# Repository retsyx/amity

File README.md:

# Amity
HDMI-CEC that works!

Control your home theater with a familiar remote, and integrate it with HomeKit or Home Assistant home automation systems.

Read the [rationale](doc/rationale.md), to know why Amity uses HDMI-CEC, and how it works.

## Prerequisites

* A Raspberry Pi 3 Model B+, or Pi Zero 2 W, or newer, that can run 64-bit Linux; with an appropriate power supply. Network connectivity is required for initial setup but not when controlling your home theater.
* A MicroSD card (4GB or larger).
* A remote control. See the [list of supported remotes](doc/supported-remotes.md).
* An [Amity Fin](hw/README.md) and an extra HDMI cable.

## Caveats

### Use Amity at Your Own Risk

!!! Using Amity may destroy your expensive HDMI equipment. Proceed at your own risk !!!

While Amity has been tested and has worked reliably with some HDMI equipment, there may still be a risk from unknown bugs. Also, when putting together Amity, you may make a mistake - this may destroy your HDMI equipment and/or your Raspberry Pi.

!!! Using Amity may destroy your expensive HDMI equipment. Proceed at your own risk !!!

### Amity is an HDMI-CEC Controller (Not a Universal Remote)

Amity is designed for a traditional setup centered around an audio/video receiver (AVR). For example, a TV connected to a receiver output, and various playback devices (i.e. media streamers, blu-ray players, and game consoles, etc.) connected to the receiver's inputs. When changing the source, the input is changed on the receiver. The HDMI-CEC protocol only allows the designated TV to select sources or devices to declare themselves as active sources. TVs do not heed arbitrary source selection commands from other devices. As a result, Amity cannot select inputs on a TV, and cannot control sources connected directly to a TV, including built-in smart TV apps. Similarly, Amity does not support HDMI ARC/eARC. If you use smart TV apps or connect devices, other than a receiver, directly to the TV inputs, Amity is not for your system.

Amity can only control devices that support HDMI-CEC! However, devices that don't support HDMI-CEC (old game consoles, for example) can still be facilitated.

### Amity is a Proof of Concept

HDMI-CEC is unevenly implemented by different manufacturers, so it doesn't always work as expected. At present, Amity can be considered a proof of concept because of the limited set of equipment it has been tested with. It works for me. It may work flawlessly with your equipment, or it may very well not. There may be ways to fix issues you encounter, and there may not. As more equipment is tested with Amity, its utility will become clearer.

Equipment that is known to be compatible with Amity:

- LG OLED TV
- Denon AVR-X3400H, AVR-X3900H
- Apple TV 4K
- Sony Playstation 4/5
- Amazon Fire TV (media player)
- Nintendo Switch (see [Strange Devices](#strange-devices))
- Wii (see [Non-HDMI Sources](#non-hdmi-sources))

## Setup

### HDMI Hardware

Amity inserts itself into the HDMI-CEC bus between the TV, and the receiver. The preferred method is to use Amity Fin.

[Acquire Amity Fin before proceeding](hw/README.md).

### Initial Installation

It is assumed that the Raspberry Pi will be a dedicated device for home theater control. It may be possible to run other services on the same Raspberry Pi but it is not supported, and is strongly discouraged.

Installation is performed with [Raspberry Pi Imager 2.0](https://www.raspberrypi.com/software/) or later (earlier versions will not work).

1. In Raspberry Pi Imager, press `App Options` (bottom left of the app).
2. In the App Options popup, press `Edit` to edit the Content Repository.
3. In the Content Repository popup, select `Use custom URL` and paste this URL into the text field: `https://github.com/retsyx/amity/releases/latest/download/amity-os.json`
4. Press `Apply & Restart`.
5. Run through the configuration wizard:
    1. Select the Raspberry Pi device you are going to use.
    2. Select the OS - `Amity`.
    3. Select the MicroSD.
    4. Set the hostname to something memorable, for example `amity`.
    5. Optionally, set localisation or leave as is.
    6. Set the username and password. The username **must** be `pi`.
    7. If using WiFi, set WiFi network information.
    8. Optionally, enable SSH, and set credentials. It is recommended to enable SSH.
6. Write the image to the MicroSD card.
7. Insert the imaged MicroSD into the Raspberry Pi, and wait for it to complete its initial boot sequence. This may take a few minutes, and a few reboots.
8. In your web browser open the Amity administration page. For example, if the hostname in Raspberry Pi Imager was configured as `amity`, then browse to `https://amity.local` (on Mac) or `https://amity` (on Windows).
 * The web browser will prompt that the site may be unsafe. This is because Amity creates a self signed security certificate for encryption. It is safe. Click on the details, and accept that the site is safe.
9. Create the Amity administration user by entering a username and password. These can be anything.
10. Login with the newly created user.

### Amity Fin Configuration

If using Amity Fin, select the 'Advanced' tab. In the 'HDMI Splice' section press the 'Use with Amity Board' button. When done, the status line should read 'Configured for Amity Board'.

### HDMI Connections

Amity connects between the TV and the receiver.

1. Disconnect the HDMI cable connecting the TV input to the receiver's output.
2. Use one HDMI cable to connect the TV's input to the Amity Fin HDMI port marked `TV`.
3. Use a second HDMI cable to connect the receiver output to the Amity Fin HDMI port marked `AVR`.

### Pairing a Remote

[Screenshot](doc/ui-images.md#remotes)

The remote **MUST** be unpaired from any other device. If the remote is paired to another device, like a streamer or TV, it will fail to work with Amity in unpredictable ways. Pairing and unpairing steps for supported remotes are listed [here](doc/supported-remotes.md). Ensure the remote is charged.

1. Select the 'Remotes' tab. The 'Remotes' panel shows if a remote or keyboard is paired, and allows pairing. Press the 'Pair' button. Wait for the initial prompt to start the pairing process on the remote.

2. Hold the remote near the Raspberry Pi.

3. Start the pairing process on the remote (see pairing steps for supported remotes [here](doc/supported-remotes.md)).

4. Follow the prompts.

If successful, the remote has been paired, and is ready for use.

### Activity Configuration

[Screenshot](doc/ui-images.md#hdmi-activities)

Amity uses a concept of activities to organize the different uses of a home theater system, similar to Harmony remotes. Every activity has a source device (i.e. Apple TV, or PlayStation), an audio output device (i.e. a receiver, or TV for volume commands), and a display (typically a TV). The remote's directional buttons are used for activity selection (on remotes that have them, the blue, red, green and yellow color buttons are also used for activity selection). This allows for up to 5 activities - 4 direction buttons and the select button.

Configuring activities is fairly straightforward thanks to HDMI-CEC.

Ensure that all home theater devices have HDMI-CEC enabled, and are discoverable. Select the 'Activities' tab, and press the 'Scan HDMI' button to list all the devices available on HDMI-CEC, and to create a recommended list of activities.

Press 'Save' to save the recommended activities.

The names of the devices are their HDMI On Screen Display (OSD) names, and are used to reference the devices in Amity configuration. Ensure that no two devices share the same name. Duplicate names are not supported, and will lead to confusion, failure, and disappointment.

Devices that don't appear in the list don't have HDMI-CEC enabled or have a very broken HDMI-CEC implementation (i.e. Nintendo Switch) that may only partially work in general.

If no devices are listed, ensure that Amity's HDMI ports are correctly attached.

#### Editing the List of Activities

The order of the activities matters. Each activity is assigned an activation button on the remote based on its position in the list of activities. The assigned activity button (and color button) on the remote is pictured next to the activity name. Read the [usage](#usage) topic to learn more. To re-order activities, press the up or down arrow buttons. To remove an activity, press the 'trash' button for that activity. To add a new activity, press the '+' button at the top of the activity list.

#### Editing an Activity

To edit an activity, press the 'Edit' button of the activity.

The fields of an activity are:

* `Name` - this can be any descriptive name you choose. The activity name is used with [HomeKit](#homekit).
* `Display` - the HDMI OSD name of the display device. Typically a TV.
* `Source` - the HDMI OSD name of the AV source device.
* `Audio` - the HDMI OSD name of the audio output device, typically a receiver.
* `Switch Device` (optional) - See [Strange Devices](#strange-devices)
* `Input` (if `Switch Device` is specified)

Remember to 'Save' the activities when done.

## Usage

Amity has two basic modes, standby, when the home theater is in standby, and active when an activity has been selected.

Note that while Amity supports multi-button and long button presses for additional functionality, the vast majority of users (e.g. family members) can ignore all of it and fully use Amity with simple button presses.

### Standby

In standby, 1 of up to 10 activities can be started. The first 5 activities are assigned to the select, and directional buttons - select, up, right, down, left. Note the order listed here matches the order of activities as specified in the Activities configuration tab. The select button starts the first activity, up the second, right the third, and so on. The next 5 activities are assigned to long presses of the same buttons, in the same order. A long press of the select button starts the sixth activity, a long press of the up button starts the seventh activity, and so on. On remotes with color buttons (blue, red, green, yellow), the color buttons are assigned to the first 4 activities.

A short press of the power button starts the first activity. A long press of the power button sends a standby command to all devices. This is useful, if a device is on when it shouldn't be.

After an activity has been selected, Amity transitions into the active mode.

Check if your remote has idiosyncrasies that may make operation a little different than described in the list of [supported remotes](doc/supported-remotes.md).

### Active

When active, all the buttons should behave as expected for the selected activity. For example, when using a PlayStation, the directional buttons navigate the PlayStation interface, select selects, back/menu backs out, and volume controls control the audio device. On remotes equipped with a touchpad, swipes can also be used.

A short press of the power button ends the activity and puts the system in standby. A long press of the power button refreshes the current activity to ensure all devices are as they should be. This is useful, if a device is not on when it should be.

For remotes that support multiple simultaneous button presses; press the power button, and then one of the activity selection buttons (select, and directional) at the same time, to jump directly from the current activity to one of the other activities, without putting the system in standby.

Check if your remote has idiosyncrasies that may make operation a little different than described in the list of [supported remotes](doc/supported-remotes.md).

## Strange Devices

HDMI-CEC devices can behave strangely. Here are some known workarounds.

### Nintendo Switch

The Nintendo switch has a minimal HDMI-CEC implementation that appears to be nearly always dormant and ignores practically every command except standby. The Switch only appears when it is powered on directly by the user, or placed in the cradle, and then it automatically requests to be displayed.

As a result, the Switch will often not show up in device scans, or be auto-configured. The solution is to create a new activity for the Nintendo Switch:

1. Press the '+' button to create a new activity.
2. Write in the activity name, for example `Play Switch`
3. Select the appropriate Display, and Audio devices.
4. Enter `NintendoSwitch` in the `Source` device field.
5. Press 'OK', and then press 'Save'.

Then to play, turn on the Switch, and select the `Play Switch` activity on the remote. Amity will do the right thing when the Switch is woken up, and announces itself. To end the activity, press the power button on the Siri remote to place the entire system in standby, including the Switch, which will go dormant again.

Sometimes, however, this may not be enough, and the Switch may still not announce its presence. For this case, the Switch can be configured similarly to a [non-HDMI source](#non-hdmi-sources).

## Non-HDMI Sources

Non-HDMI sources can be minimally supported, if the receiver supports input selection over HDMI-CEC. An activity for a non-HDMI source can still control the display and receiver, including power and volume, but cannot control the power of the non-HDMI source or send it menu commands. This limited support is particularly useful for old game consoles that require the use of their own game controllers in any case so a universal remote to control them is of limited value.

To support a non-HDMI source, Amity can be configured to select the input on the receiver. In the activity settings:

1. Select the receiver as the `Switch Device`.
2. Specify the `Input` number.

This functionality depends on the receiver supporting the feature, and on knowing the correct value for the input. On Denon AVR-X3400H and AVR-X3900H receivers the numeric input values can be configured in the receiver setup menus. From the factory, the numeric input values on a Denon AVR-X3400H correspond to the named inputs as follows:

1. CBL/SAT
2. DVD
3. Blu-ray
4. Games
5. Media Player
6. Aux 2
7. ?
8. Aux 1

?. CD

## HomeKit

[Screenshot](doc/ui-images.md#homekit)

Amity can be integrated with HomeKit as a TV accessory. This allows controlling Amity with Siri, and integrating Amity into HomeKit automations. In addition, if using a BLE remote that supports battery level reporting, the remote battery level, and low battery warnings are reported to HomeKit.

It is highly recommended to complete all activity configuration, and setup before adding Amity into HomeKit.

Select the 'HomeKit' tab, and press 'Enable'. Follow the instructions to pair Amity with HomeKit.

## Home Assistant / MQTT

[Screenshot](doc/ui-images.md#homeassistant-mqtt)

Amity can be integrated with Home Assistant. This allows integrating Amity into Home Assistant automations.  In addition, if using a BLE remote that supports battery level reporting, the remote battery level and charge state is reported to Home Assistant.

It is highly recommended to complete all activity configuration, and setup before adding Amity into Home Assistant.

While Amity's MQTT implementation is tailored for seamless operation with Home Assistant, it can be used with any MQTT based system.

Select the 'MQTT' tab, configure the required MQTT settings and press 'Enable'.

## Backup & Restore

For backup, Amity configuration can be downloaded in the 'Configuration' section of the 'Advanced' tab. To restore a backup, use the upload feature in the same tab.

## CLI Management

Amity can also be [managed through the terminal](doc/CLI.md).

## License

Amity source code is licensed under the [GPLv3](LICENSE).

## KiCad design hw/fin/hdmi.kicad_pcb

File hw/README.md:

# HDMI-CEC Hardware

!!! Using Amity may destroy your expensive HDMI equipment. Proceed at your own risk !!!

The recommended HDMI-CEC hardware for Amity is Amity Fin. It is the easiest way to connect the Raspberry Pi to your home theater's HDMI.

Alternatively, [Amity Board](board.md) can be used with a wiring harness to connect it to the Raspberry Pi.

It is also possible, but not recommended, to create a standalone wiring harness by stripping and cutting a standard [HDMI cable](cable.md).

Note that all of the commonly available HDMI breakout boards advertised for sale are not designed to pass through high-speed A/V signals, and break video display in an actual home theater.

## Amity Fin

Amity Fin is a 4 layer PCB that includes onboard 27K ohms pullup resistors to conform to the HDMI-CEC specification. When used with the board, Amity must be configured to disable the Raspberry Pi internal GPIO pullup resistors.

### Caveats

Amity Fin is experimental. It has been very lightly tested to work for video up to 4K@60Hz Dolby Vision. EMI is unknown, and it may have other unknown bugs. If you are an experienced HW engineer interested in improving the board design, you are invited to submit improvements.

### Obtaining Amity Fin

A [turnkey project](https://www.pcbway.com/project/shareproject/Amity_Fin_v1_0_a3868150.html) is available for immediate PCB manufacture and component assembly.

Alternatively, you can manufacture Amity Fin with your preferred method. Amity Fin KiCAD files are [here](fin). In the [mfr](fin/mfr) folder are the manufacturing files, and an example BOM for submission to a PCB manufacturer/assembler (the BOM will likely need to be tailored to the manufacturer's requirements).

#### BOM

* 2x [HDMI-A connectors](https://www.digikey.com/en/products/detail/amphenol-cs-fci/10029449-001RLF/1001325)
* 2x [0603 SMD 27K ohms resistors](https://www.digikey.com/en/products/detail/bourns-inc/CR0603-JW-273ELF/3784345)
* 2x [0603 SMD diodes](https://www.digikey.com/en/products/detail/taiwan-semiconductor-corporation/TS4148-RCG/7359811)
* 1x [2.54mm 2x3 connector header](https://www.digikey.com/en/products/detail/sullins-connector-solutions/PPTC032LJBN-RC/775975)

### Mounting Amity Fin

Amity Fin fits over Raspberry Pi header pins 13 - 18. It is mounted with the Amity A graphic facing out from the Raspberry Pi, 6 pins away from the right edge of the header. See the photo for an illustration.

### Amity Fin Mounted on a Raspberry Pi 5

Note the Amity A graphic facing out from the Raspberry Pi, and the 6 pins to the right of the Fin.

### Amity Fin Mounted on a Raspberry Pi Zero 2 W in a Case

STEP files for a 3D printable case for a Raspberry Pi Zero with Amity Fin is available [here](case/).

### Configuring Amity

After [initial installation](../README.md#initial-installation) of Amity, and before plugging in the HDMI connections, Amity must be configured to use Amity Fin.

In the Amity management UI, select the 'Advanced' tab. In the 'HDMI Splice' section press the 'Use with Amity Board' button. When done, the status line should read 'Configured for Amity Board'.

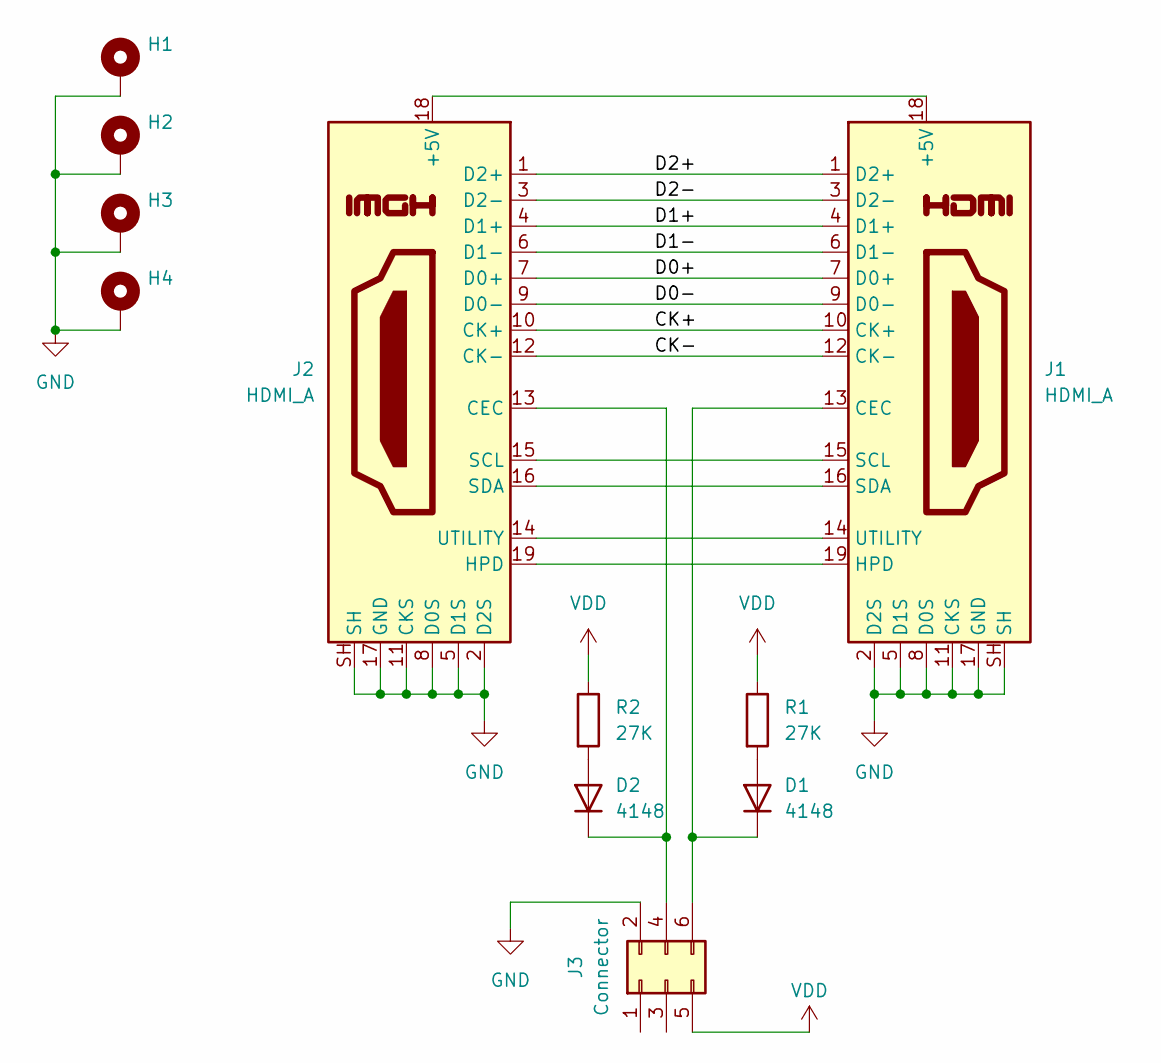
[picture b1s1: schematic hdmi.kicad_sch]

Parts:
D1, D2: 4148; D_0603_1608Metric
H1, H2, H3, H4: MountingHole_2.5mm_Pad
J1, J2: HDMI_A; HDMI_A_Amphenol_10029449-x01xLF_Horizontal
J3: Connector; PinSocket_2x03_P2.54mm_Horizontal
R1, R2: 27K; R_0603_1608Metric

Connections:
/CK+: J1.10 (CK+), J2.10 (CK+)
/CK-: J1.12 (CK-), J2.12 (CK-)
/D0+: J1.7 (D0+), J2.7 (D0+)
/D0-: J1.9 (D0-), J2.9 (D0-)
/D1+: J1.4 (D1+), J2.4 (D1+)
/D1-: J1.6 (D1-), J2.6 (D1-)
/D2+: J1.1 (D2+), J2.1 (D2+)
/D2-: J1.3 (D2-), J2.3 (D2-)
GND: H1.1, H2.1, H3.1, H4.1, J1.2 (D2S), J1.5 (D1S), J1.8 (D0S), J1.11 (CKS), J1.17 (GND), J1.SH, J2.2 (D2S), J2.5 (D1S), J2.8 (D0S), J2.11 (CKS), J2.17 (GND), J2.SH, J3.2
unnamed: D1.2 (A), R1.2
unnamed: D1.1 (K), J1.13 (CEC), J3.6
unnamed: D2.2 (A), R2.2
unnamed: D2.1 (K), J2.13 (CEC), J3.4
unnamed: J1.18 (+5V), J2.18 (+5V)
unnamed: J1.19 (HPD), J2.19 (HPD)
unnamed: J1.15 (SCL), J2.15 (SCL)
unnamed: J1.16 (SDA), J2.16 (SDA)
unnamed: J1.14 (UTILITY), J2.14 (UTILITY)
VDD: J3.5, R1.1, R2.1

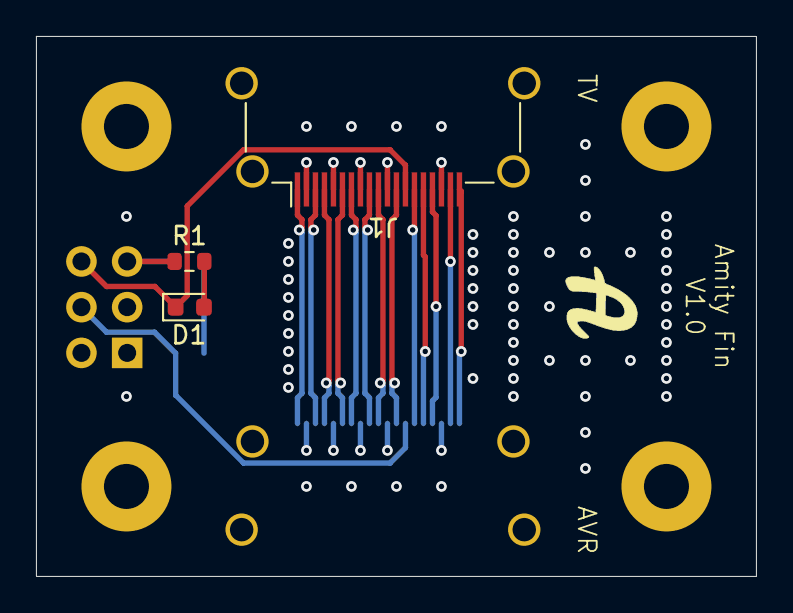
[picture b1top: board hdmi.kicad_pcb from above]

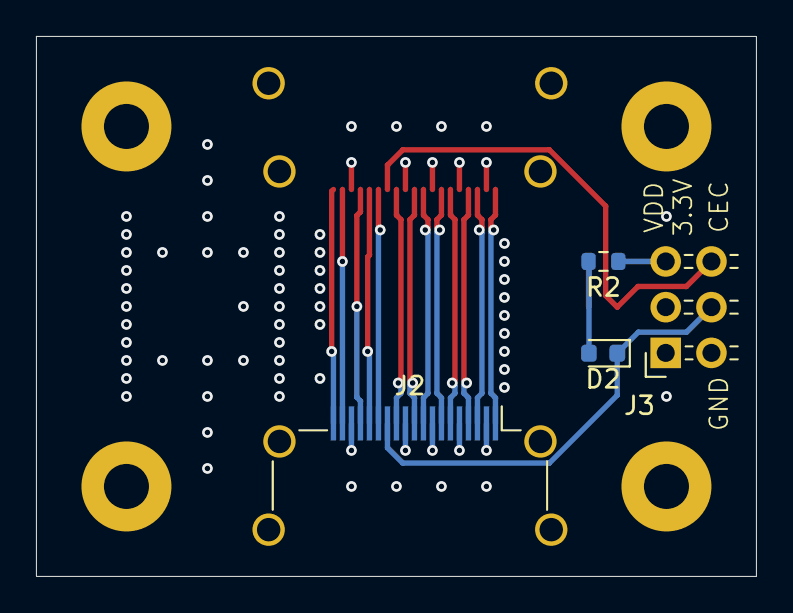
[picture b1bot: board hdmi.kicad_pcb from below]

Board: 4 copper layers, 40.0 x 30.0 mm, 11 parts (4 on the bottom side), 19 nets.

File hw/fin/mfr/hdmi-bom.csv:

Reference,Value,Datasheet,Footprint,Qty,DNP
"D1,D2",4148,https://www.digikey.com/en/products/detail/taiwan-semiconduc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,Diode_SMD:D_0603_1608Metric,2,
"J1,J2",HDMI_A,https://www.digikey.com/en/products/detail/amphenol-cs-fci/1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,Connector_Video:HDMI_A_Amphenol_10029449-x01xLF_Horizontal,2,
J3,Connector,https://www.digikey.com/en/products/detail/sullins-connector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,Connector_PinSocket_2.54mm:PinSocket_2x03_P2.54mm_Horizontal,1,
"R1,R2",27K,https://www.digikey.com/en/products/detail/bourns-inc/CR0603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,Resistor_SMD:R_0603_1608Metric,2,

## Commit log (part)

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2024-07-07 Add UI
2024-07-19 Use new multi-adapter python-cec architecture
2024-07-19 Handle BrokenPipeError in Siri remote loop
2024-07-19 Prevent keyboard power keys from powering down the system
2024-07-19 Handle device power status requests
2024-07-19 Readme additions
2024-07-19 Add pressure threshold to gesture recognizers and config
    Also add echo_test.py
2024-07-19 Add Linux kernel build/install scripts
    Tools for compiling and installing Linux on Raspberry Pi.
    Needed to recompile kernel for cec-gpio support.
2024-07-22 Add SET INPUT fallback configuration option for CEC challenged devices
2024-07-22 Refetch OSD name for mystery devices that update their physical address
2024-07-22 Request active source from the TV
2024-07-22 OSD name is handled by the kernel after we set it at the beginning
2024-08-04 setup_amity downloads, and installs cec-gpio kernel and overlay
2024-08-04 Add keyboard handling for digits
2024-08-04 Unified config
2024-08-20 Add .gitignore
2024-08-22 Fix gesture handling
    Fix swipe gesture end check so that it actually runs.
    Accumulate key counts so that multiple gesture events with differing counts don't clobber each other.
2024-08-25 Simplify key press handling with async
    Benefit from async CEC I/O. Remove timers and make key handling code purely async.
2024-09-01 Cleanup old devices when physical address is reported.
    A non-compliant device may 'disappear' and another device may inherit its physical address.
    So if a device declares a physical address recorded for another device, assume the other device is dormant,
    and remove it. If the device is needed, a missing device scan should hopefully pick it up again.
2024-09-03 Don't handle CEC RX in ControllerImpl until fully inited
2024-09-04 Add restart command to setup_amity
2024-09-04 Don't choke on spurious key releases
2024-09-06 Keyboard shouldn't choke on unexpected keys
2024-09-08 reworded readme
2024-09-10 Move from bluepy to bluepy3
2024-09-15 Initial PCB design for tapping into HDMI-CEC
    Board that breaks out the CEC wire from an HDMI bundle so that it can be plugged into a Raspberry Pi,
    without meaningfully degrading the A/V signal that is passed through.
    Tested successfully with 4K@60Hz/Dolby.
    Open items:
    1. Missing 27K Ohm +/- 5% pullup resistors instead of using Raspberry Pi's internal ~60K Ohm resistors.
    2. Raspberry Pi hat form factor of some kind, or other design amenable to a more complete plug and play
2024-09-18 Add board schematic in PDF
    Allow quick glance at schematic without having to open the entire probject with KiCad.
2024-09-29 import cleanup
2024-10-02 Release counted key state when waiting for key release
2024-10-10 PCB v2
    4 Layers. More regular board dimensions. Thicker, straighter, shorter, better separated, equal length,
    high speed traces.
    No DRC violations.
2024-10-22 Tweak readmes
2024-10-24 Call our MicroSD card in readme
2024-10-25 Revert "Play pause button should play/pause instead of select"
    This reverts commit c3fce2a0056a154618bf176c719eee4d54117049.
2024-10-27 Fix readme typos
2024-10-30 Add 6.6.51 header path to configure_gpio. This is a temporary fix as these paths need to be found automatically.
2024-11-02 configure_gpio uses last linux header path instead of first
2024-11-07 Tweaks
    Add omitted files from pycache warmup in setup_amity.
    echo_test.py disconnects the remote with bluetoothctl before trying to connect to it.
2024-11-22 Manage config backups
    After creating a backup, delete old backups so that only 'config.max_backups' remain.
    Default max_backups is 10, and can be configured by specifying 'config.max_backups' in
    the config file.
2024-11-26 configure_gpio fix
    When external pullup is specificed, ensure that no on board pull up is explicitly set in the GPIO kernel configuration.
2024-11-26 Add configure_gpio status command to get current GPIO pin pullup configuration
2024-12-01 Streamlined kernel build scripts
    1. Trimemd to build only 64-bit kernels.
    2. Streamlined for non-interactive use.
    3. Added setup-build-env.sh to install the required packages for building the kernels.
    4. Added functionality to specify kernel config changes in config-overlay file.
2024-12-02 Make sure to disconnect Siri Remote bluetooth before attempting to connect
    The system will automatically connect to the remote and block us from connecting to it.
    So ensure nothing is connected to the remote before attempting to connect to it.
2024-12-06 Fix HDMI scan on unconnected HDMI ports
2024-12-06 Comprehensive, unified setup and image build scripts
    Running build/build-image.sh (preferably on a beefy Ubuntu machine) compiles the required kernels,
    and builds a ready image for writing to an SD card for immediate use on a RPi. Further Amity
    configuration is done through the web interface.
    For manual setup on an already running RPi, downloading, and running setup_amity may work much as before
    but it is not tested, and will likely be dropped since maintaining the kernels separately online is extra
    work that doesn't yield much benefit. Building a full image is very fast with the right hardware.
2024-12-07 Readme updates
2025-07-29 Increase max time of authentication password hashing to 1 second so authentication doesn't fail on slower devices
2025-08-03 Update raspios lite base image to latest
2025-08-11 Update README.md
    Change Amity byline.
2025-11-24 Source thief protection for activity with no source...
    Activities with no configured source are valid so source thief protection should apply correctly
    to them as well. This change fixes source protection to not confuse an activity with no configured source
    with an acitivity with a source that can't be found.
2025-11-24 Note Raspberry Pi Imager 2.0 breakage
2025-11-25 Explicity declare the root path ('/') ui.page()
    NiceGUI was previously lenient with global ui element declarations by automatically placing them in the
    root path. As of version 3(?), NiceGUI disallows declaring any ui.pages if any other ui elements are
    declared globally. So explicitly declare the main UI page with a ui.page() decorator. Also, pin nicegui
    to latest version, 3.3.1.
2025-12-01 Add lg-magic driver to build to allow using LG Magic Remotes
2025-12-01 Modify keyboard required key check to allow for alternatives
    The LG remote doesn't support KEY_POWER but does support KEY_SLEEP instead. Make KEY_POWER and KEY_SLEEP
    viable alternatives for the same requirement.
2025-12-01 Use F/color keys for activity selection
2025-12-03 Add keyboard battery level monitoring
    If a keyboard is a BLE keyboard that was paired with the pair_tool then query the bluetooth stack for the
    keyboard's battery level. If the keyboard supports it, report it.
    Adding battery level reporting for the keyboard necessitates requiring only one active remote at any
    given time to avoid multiple battery levels being reported.
    From now, only one BLE keyboard or one Siri remote can be used, by default. For debugging and testing,
    multiple remotes can still be paired with the 'keep' command line argument to pair_remote, and keyboard
2025-12-04 Another nicegui surprise
    The file upload event has changed...
2025-12-04 Update documentation to be remote agnostic.
    Add a list of supported remotes and a documentation page for each remote.
2025-12-06 Clarify TV source selection language
2025-12-09 Pin forward nicegui to 3.4.0
2025-12-12 Work around nicegui memory leak.
    See:
    https://github.com/zauberzeug/nicegui/discussions/5127
    https://github.com/zauberzeug/nicegui/issues/4521
2025-12-15 Fix nicegui/fastapi version conflict
2025-12-17 Emulate play/pause state to workaround play/pause problem
    Most remotes have a single play/pause button. However, HDMI-CEC doesn't seem to have a play/pause key
    code equivalent. Instead, HDMI-CEC has discrete play and pause key codes.
    Until now, the workaround has been to map play/pause to the select key which behaves more or less as
    expected in most cases. Particularly, when watching video. However, it fails when playing music on a media
    player while browsing other elements of the UI that are not the playback control. Select will select
    whatever is displaying in the UI instead of actually pausing or resuming the background music. This requires
2025-12-18 Remove defunct setup_amity
2025-12-23 Google TV Remote support
2026-01-23 Amity Fin v1.0
    Refactor Amity Board into a fin that rises up and out from the Raspberry Pi header directly. The fin removes
    the need for a wiring harness and makes it easier to put together the hardware.
    The unusual form factor is an easy way to ensure that the HDMI connectors and cables are far enough away
    from the Raspberry Pi board so that there is no interference.
2026-01-24 Add keyboard handling for F1-F4 keys
2026-02-03 Catch EBUSY exception in CEC ioctl
    If the kernel's CEC command queue fills up, the ioctl() returns EBUSY. Python throws an exception.
    Catch the exception and mark the message as TX failed.
2026-02-03 Build bluepy3 helper as part of setup-amity-core instead of deferring to when installed
2026-02-07 Workaround an ancient bug in btmgmt
    btmgmt will apparently freeze if it doesn't have a stdin. This fails pair_remote when called from
    the management UI. The workaround is to pipe in nothing with echo.
2026-02-07 Fix bluetooth reconnection bogusness
    Trixie doesn't seem to automatically reconnect to devices unless bluetoothctl has been called at
    least once to connect to them. So, immediately after pairing, disconnect, mark the device trusted and
    connect to it with bluetoothctl.
2026-02-07 Bump nicegui to 3.7.1
2026-02-13 Use start_new_session instead of preexec_fn os.setsid() for launching pair_remote from remotes.py
2026-02-14 Fix solarcell comment typo
2026-02-14 cec.py tweaks
2026-02-14 SolarCell fixups
2026-02-14 In hdmi.py don't import cec.Device as Device
    Because we declare our own Device in hdmi.
2026-02-14 config.py tweaks
2026-02-14 Replace config asserts with proper exceptions
2026-02-15 remote.py type annotation
2026-02-15 remote_adapter.py type annotation
2026-02-15 homekit.py type annotation
2026-02-15 solarcell.py type annotation
2026-02-15 tools.py type annotation
2026-02-15 gestures.py type annotation
2026-02-15 keyboard.py type annotation
2026-02-15 service.py type annotation
2026-02-16 bump fastapi version to 3.7.1
2026-02-17 MQTT managmenet, add a discard changes button, and some code cleanup
2026-02-18 Ensure venv created at image build doesn't modify .gitignore
2026-02-18 evdev_input.py remove unused imports
2026-02-18 mqtt_tool.py type annotation
2026-02-18 management/activities.py type annotation
2026-02-18 management/mqtt.py type annotation
2026-02-18 management/advanced.py type annotation
2026-02-18 mqtt_tool.py report if amity is not running when MQTT is enabled
2026-02-18 management/remotes.py type annotation
2026-02-18 management/main.py type annotation
2026-02-19 Github action to build the Amity image.
2026-02-19 Github action to create a release
2026-02-19 Add admin UI screenshots
2026-03-10 Update rationale.md with the reason for using Amity Fin
